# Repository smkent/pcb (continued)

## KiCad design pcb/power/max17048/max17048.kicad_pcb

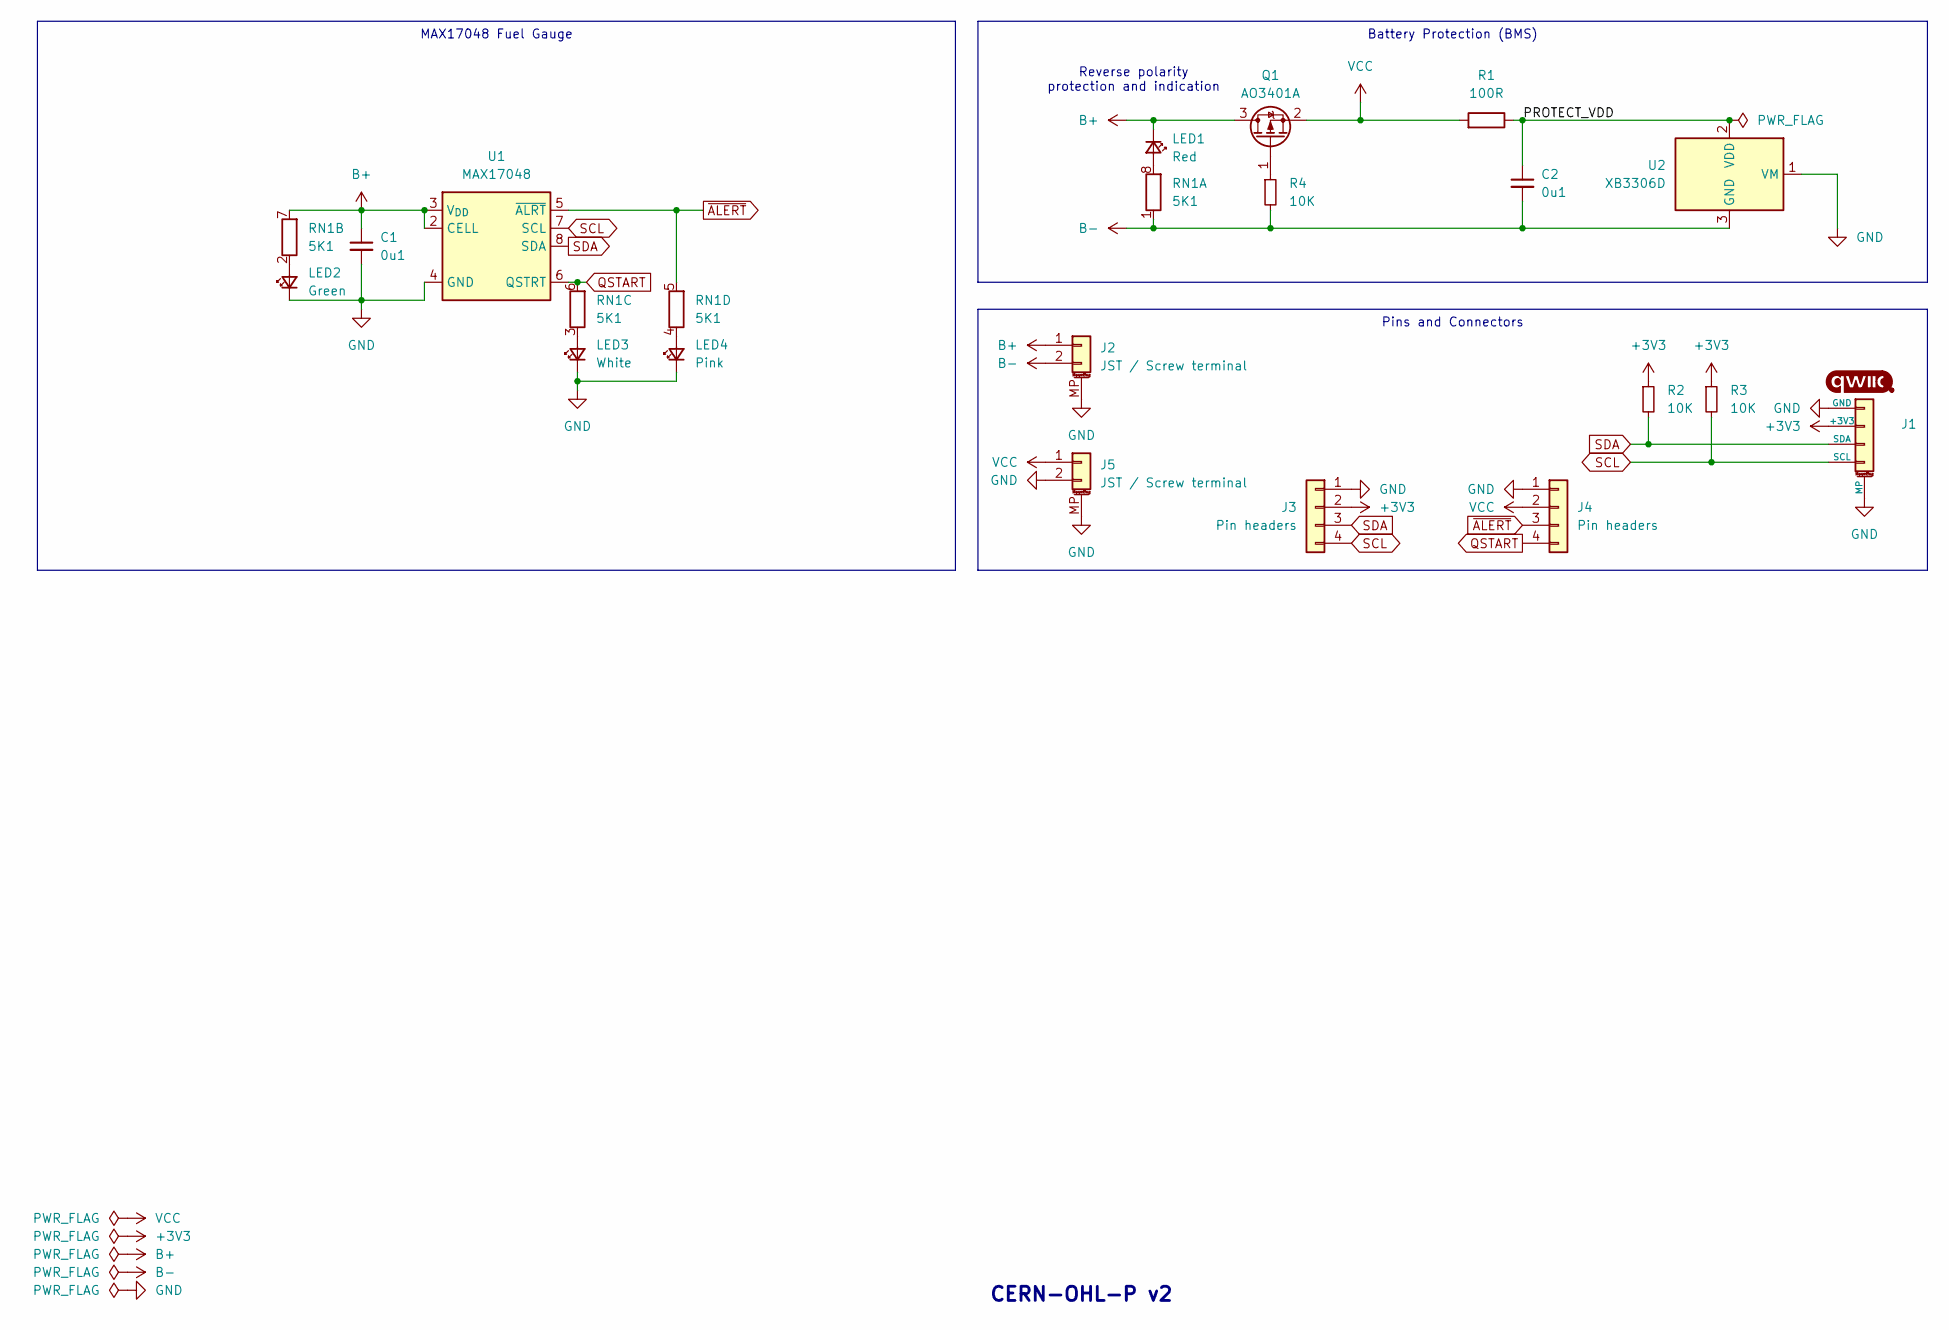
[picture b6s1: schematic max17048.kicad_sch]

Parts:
C1, C2: 0u1; C_0603_1608Metric
J1: Qwiic; Qwiic-SMD-horizontal-logo-bottom-pinout
J2, J5: JST / Screw terminal; Conn_Combo_TerminalBlock_JST-1x02-XH_PH-pad2gnd
J3, J4: Pin headers; PinHeader_1x04_P2.54mm_Vertical_simple
LED1: Red; LED_0603_1608Metric_Pad1.05x0.95mm_HandSolder_simple; LCSC Part C2286
LED2: Green; LED_0603_1608Metric_Pad1.05x0.95mm_HandSolder_simple; LCSC Part C2286
LED3: White; LED_0603_1608Metric_Pad1.05x0.95mm_HandSolder_simple; LCSC Part C2286
LED4: Pink; LED_0603_1608Metric_Pad1.05x0.95mm_HandSolder_simple; LCSC Part C2286
Q1: AO3401A; SOT-23
R1: 100R; R_0603_1608Metric; LCSC Part C25076
R2, R3, R4: 10K; R_0603_1608Metric
RN1: 5K1; R_Array_Convex_4x0603
U1: MAX17048; TDFN-8-1EP_2x2mm_P0.5mm_EP0.8x1.2mm; LCSC Part C2682616
U2: XB3306D; SOT-23; LCSC Part C2759992

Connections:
+3V3: J1.2 (+3V3), J3.2, R2.1, R3.1
/PROTECT_VDD: C2.1, R1.1, U2.2 (VDD)
B+: C1.1, J2.1, LED1.1 (K), Q1.3 (D), RN1.7 (R2.2), U1.2 (CELL), U1.3 (V_{DD})
B-: C2.2, J2.2, R4.2, RN1.1 (R1.1), U2.3 (GND)
GND: C1.2, J1.1 (GND), J1.MP, J2.MP (MountPin), J3.1, J4.1, J5.2, J5.MP (MountPin), LED2.1 (K), LED3.1 (K), LED4.1 (K), U1.1 (CTG), U1.4 (GND), U1.9 (EP), U2.1 (VM)
unnamed: LED1.2 (A), RN1.8 (R1.2)
unnamed: LED2.2 (A), RN1.2 (R2.1)
unnamed: LED3.2 (A), RN1.3 (R3.1)
unnamed: LED4.2 (A), RN1.4 (R4.1)
unnamed: Q1.1 (G), R4.1
QSTART: J4.4, RN1.6 (R3.2), U1.6 (QSTRT)
SCL: J1.4 (SCL), J3.4, R3.2, U1.7 (SCL)
SDA: J1.3 (SDA), J3.3, R2.2, U1.8 (SDA)
VCC: J4.2, J5.1, Q1.2 (S), R1.2
~ALERT: J4.3, RN1.5 (R4.2), U1.5 (~ALRT)

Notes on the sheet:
MAX17048 Fuel Gauge
Pins and Connectors
Battery Protection (BMS)
CERN-OHL-P v2
Reverse polarity protection and indication

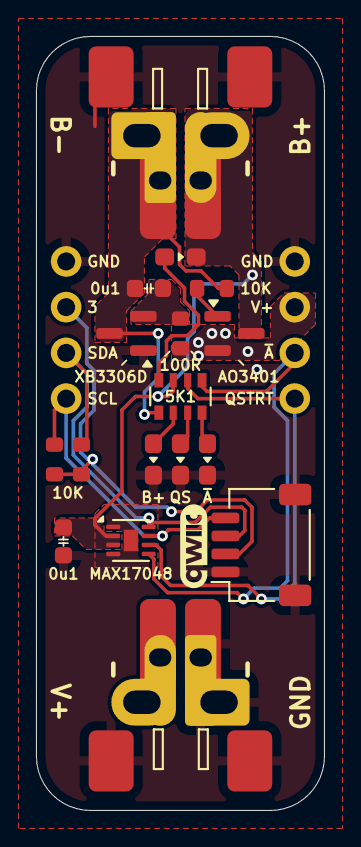
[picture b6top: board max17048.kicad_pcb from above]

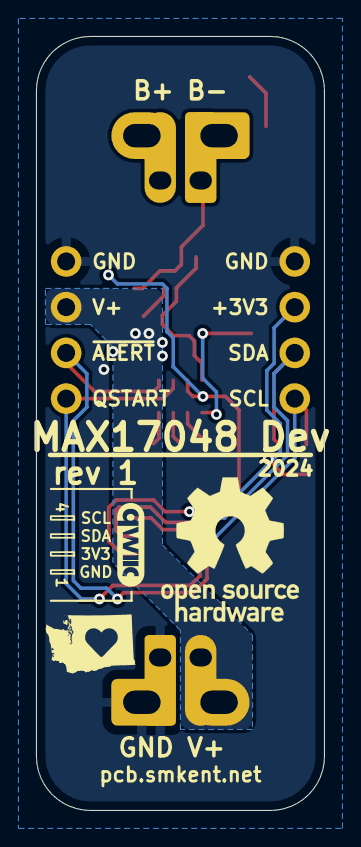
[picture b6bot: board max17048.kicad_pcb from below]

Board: 2 copper layers, 16.0 x 43.0 mm, 19 parts (2 on the bottom side), 15 nets.

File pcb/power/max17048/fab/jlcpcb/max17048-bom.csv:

Comment,Designator,Footprint,LCSC
White,LED3,custom:LED_0603_1608Metric_Pad1.05x0.95mm_HandSolder_simple,C2286
10K,"R2,R3,R4",custom:R_0603_1608Metric_simple,
0u1,"C1,C2",custom:C_0603_1608Metric,
100R,R1,custom:R_0603_1608Metric_simple,C25076
Red,LED1,custom:LED_0603_1608Metric_Pad1.05x0.95mm_HandSolder_simple,C2286
5K1,RN1,Resistor_SMD:R_Array_Convex_4x0603,
Qwiic,J1,connectors:Qwiic-SMD-horizontal-logo-bottom-pinout,
Green,LED2,custom:LED_0603_1608Metric_Pad1.05x0.95mm_HandSolder_simple,C2286
JST / Screw terminal,"J2,J5",custom:Conn_Combo_TerminalBlock_JST-1x02-XH_PH-pad2gnd,
Pink,LED4,custom:LED_0603_1608Metric_Pad1.05x0.95mm_HandSolder_simple,C2286
Pin headers,"J3,J4",custom:PinHeader_1x04_P2.54mm_Vertical_simple,
AO3401A,Q1,custom:SOT-23_simple,
XB3306D,U2,custom:SOT-23_simple,C2759992
MAX17048,U1,custom:TDFN-8-1EP_2x2mm_P0.5mm_EP0.8x1.2mm,C2682616

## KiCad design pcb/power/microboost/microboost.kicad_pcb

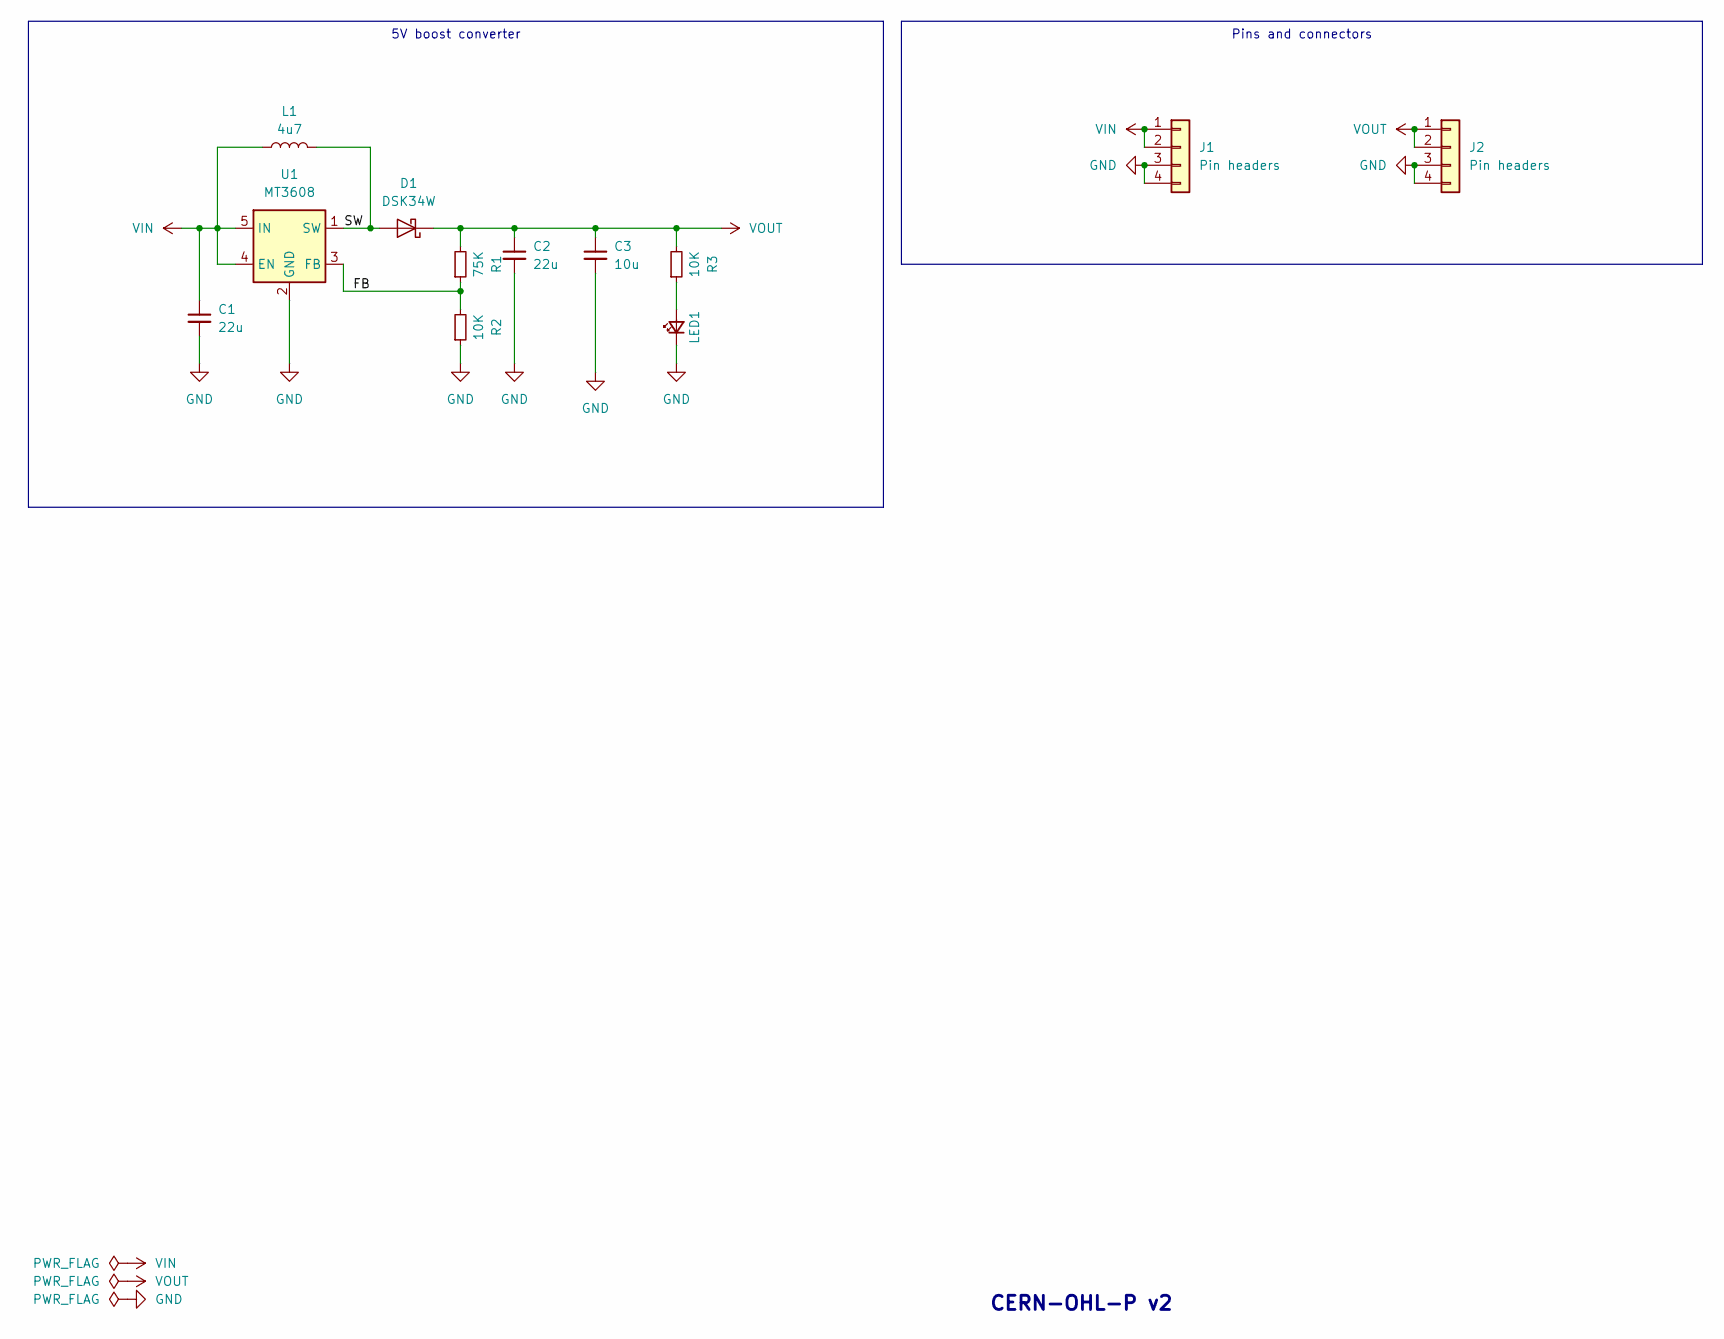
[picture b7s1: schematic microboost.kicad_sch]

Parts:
C1, C2: 22u; C_0805_2012Metric_Pad1.18x1.45mm_HandSolder
C3: 10u; C_0603_1608Metric_Pad1.08x0.95mm_HandSolder
D1: DSK34W; D_SOD-123F; LCSC Part C3014041
J1, J2: Pin headers; PinHeader_1x04_P2.54mm_Vertical_simple_pad3,4gnd
L1: 4u7; L_1008_2520Metric
LED1: LED_Small; LED_0603_1608Metric_Pad1.05x0.95mm_HandSolder_simple
R1: 75K; R_0603_1608Metric_Pad0.98x0.95mm_HandSolder
R2, R3: 10K; R_0603_1608Metric_Pad0.98x0.95mm_HandSolder
U1: MT3608; SOT-23-6; LCSC Part C84817

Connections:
/FB: R1.1, R2.2, U1.3 (FB)
/SW: D1.2 (A), L1.2, U1.1 (SW)
GND: C1.2, C2.2, C3.2, J1.3, J1.4, J2.3, J2.4, LED1.1 (K), R2.1, U1.2 (GND)
unnamed: LED1.2 (A), R3.1
VIN: C1.1, J1.1, J1.2, L1.1, U1.4 (EN), U1.5 (IN)
VOUT: C2.1, C3.1, D1.1 (K), J2.1, J2.2, R1.2, R3.2

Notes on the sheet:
Pins and connectors
5V boost converter
CERN-OHL-P v2

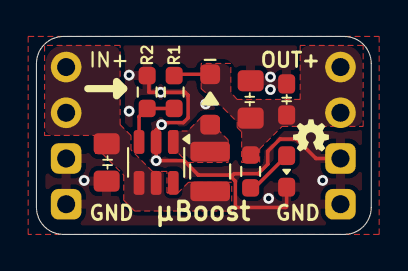
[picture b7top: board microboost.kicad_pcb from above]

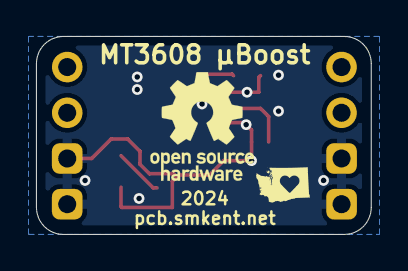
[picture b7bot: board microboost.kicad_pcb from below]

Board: 2 copper layers, 18.6 x 11.0 mm, 12 parts (2 on the bottom side), 6 nets.

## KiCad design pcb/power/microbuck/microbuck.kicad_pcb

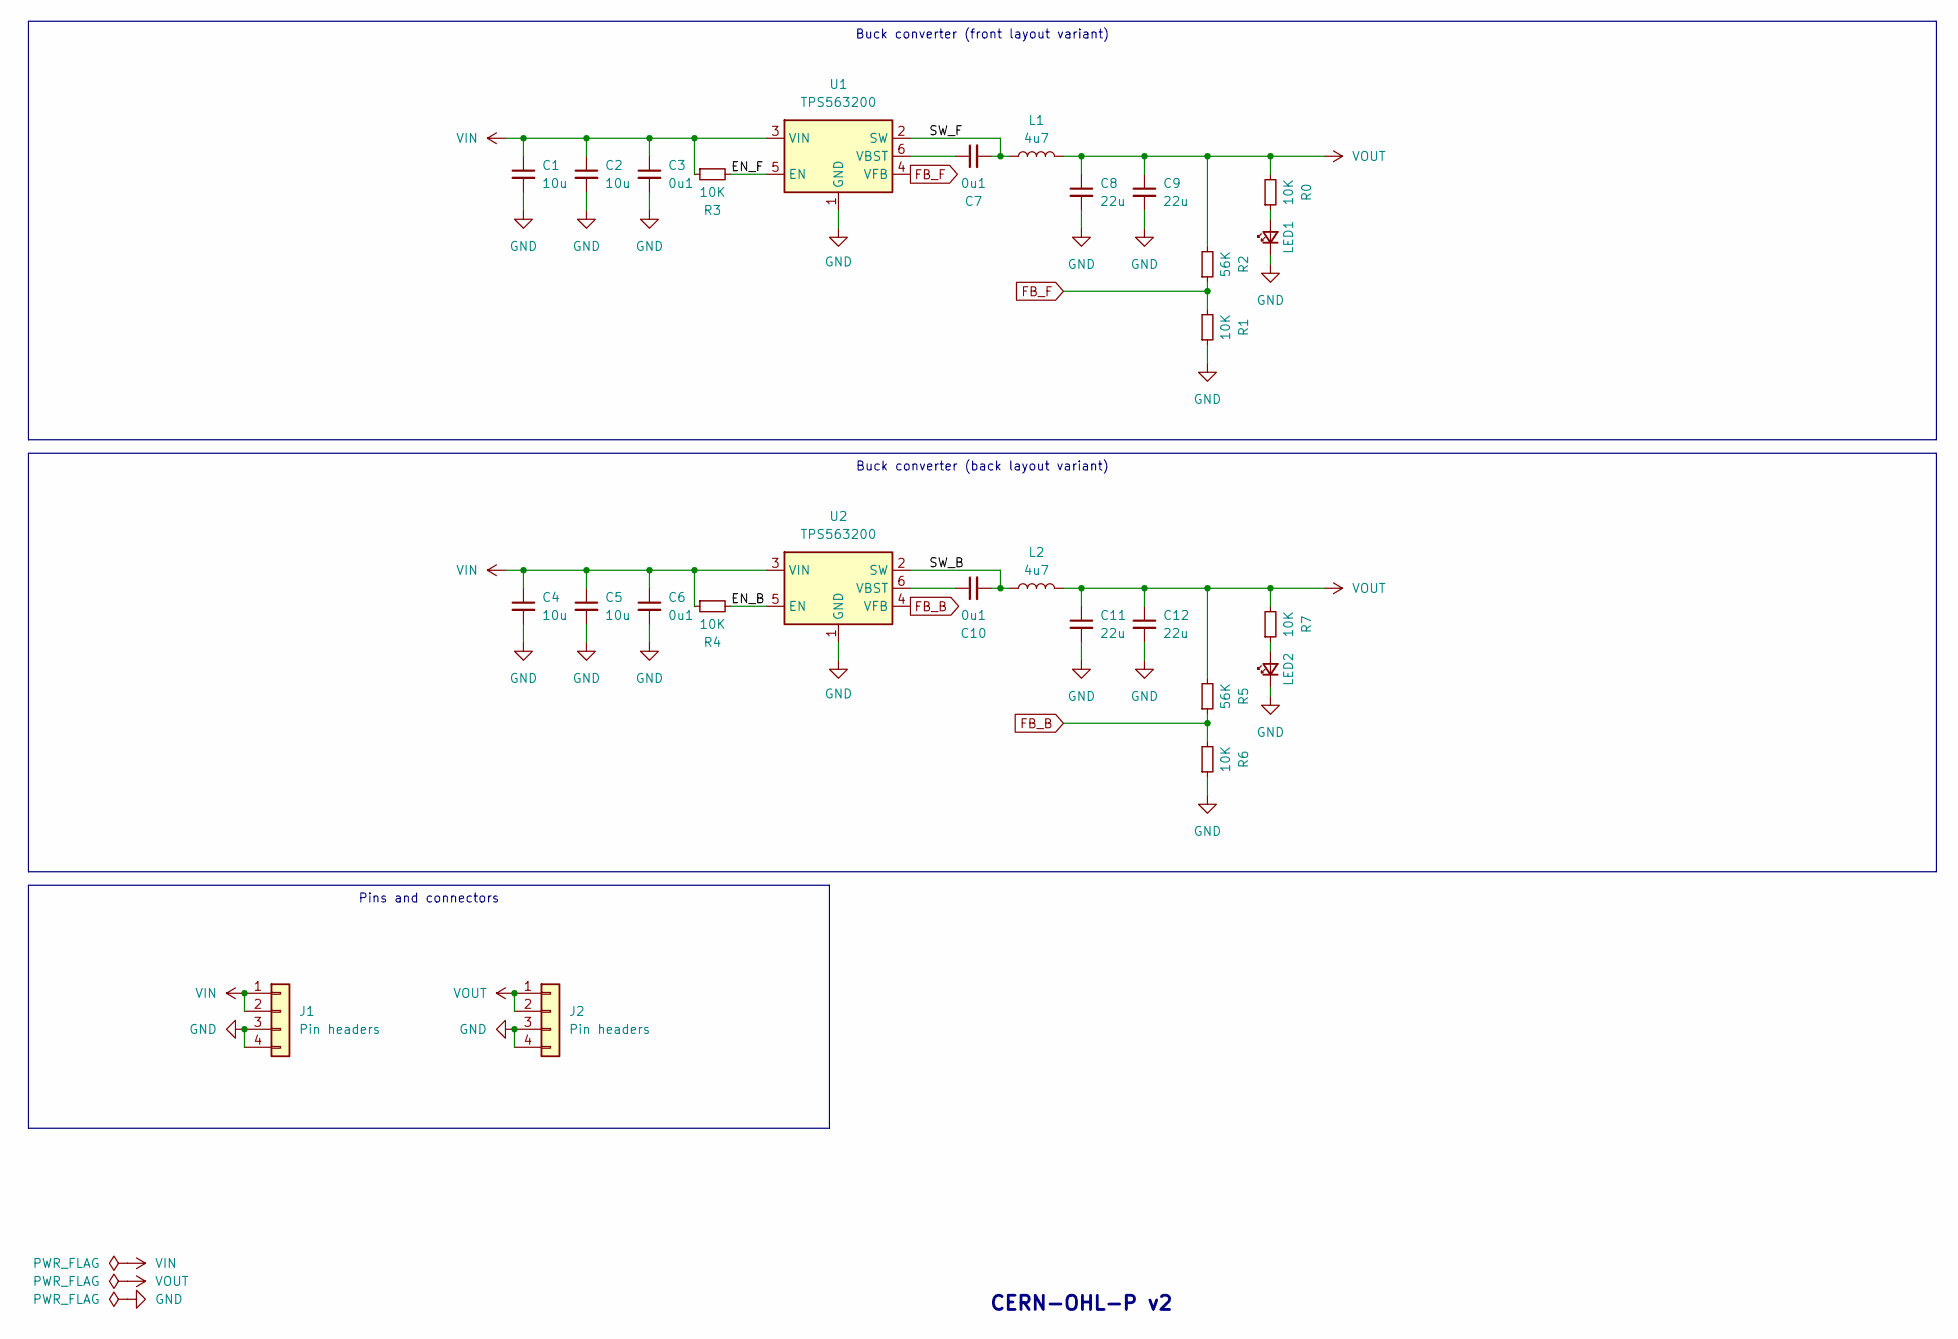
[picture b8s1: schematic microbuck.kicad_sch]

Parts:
C1, C2, C4, C5: 10u; C_0603_1608Metric_Pad1.08x0.95mm_HandSolder
C3, C6, C7, C10: 0u1; C_0603_1608Metric_Pad1.08x0.95mm_HandSolder
C8, C9, C11, C12: 22u; C_0603_1608Metric_Pad1.08x0.95mm_HandSolder
J1, J2: Pin headers; PinHeader_1x04_P2.54mm_Vertical_simple_pad3,4gnd
L1, L2: 4u7; L_1008_2520Metric
LED1, LED2: LED_Small; LED_0603_1608Metric_Pad1.05x0.95mm_HandSolder_simple
R0, R1, R3, R4, R6, R7: 10K; R_0603_1608Metric_Pad0.98x0.95mm_HandSolder
R2, R5: 56K; R_0603_1608Metric_Pad0.98x0.95mm_HandSolder
U1, U2: TPS563200; SOT-23-6

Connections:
/EN_B: R4.2, U2.5 (EN)
/EN_F: R3.2, U1.5 (EN)
/SW_B: C10.2, L2.1, U2.2 (SW)
/SW_F: C7.2, L1.1, U1.2 (SW)
FB_B: R5.1, R6.2, U2.4 (VFB)
FB_F: R1.2, R2.1, U1.4 (VFB)
GND: C1.2, C2.2, C3.2, C4.2, C5.2, C6.2, C8.2, C9.2, C11.2, C12.2, J1.3, J1.4, J2.3, J2.4, LED1.1 (K), LED2.1 (K), R1.1, R6.1, U1.1 (GND), U2.1 (GND)
unnamed: LED1.2 (A), R0.1
unnamed: LED2.2 (A), R7.1
unnamed: C7.1, U1.6 (VBST)
unnamed: C10.1, U2.6 (VBST)
VIN: C1.1, C2.1, C3.1, C4.1, C5.1, C6.1, J1.1, J1.2, R3.1, R4.1, U1.3 (VIN), U2.3 (VIN)
VOUT: C8.1, C9.1, C11.1, C12.1, J2.1, J2.2, L1.2, L2.2, R0.2, R2.2, R5.2, R7.2

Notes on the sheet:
Pins and connectors
Buck converter (front layout variant)
Buck converter (back layout variant)
CERN-OHL-P v2

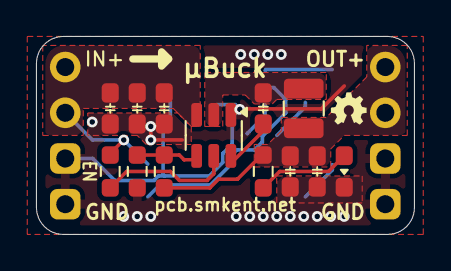
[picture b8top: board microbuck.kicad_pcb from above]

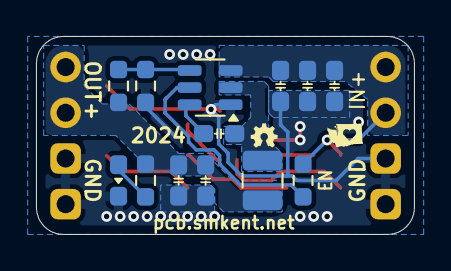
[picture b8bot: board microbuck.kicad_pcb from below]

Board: 2 copper layers, 21.0 x 11.0 mm, 28 parts (15 on the bottom side), 13 nets.
